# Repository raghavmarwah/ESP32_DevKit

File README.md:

# ESP32 Development Board Clone

This is project #3 for the course [KiCAD like a Pro](https://techexplorations.com/so/kicad-like-a-pro-3rd-edition/). In this project, I created my own version of the very popular [ESP32 development kit](https://docs.espressif.com/projects/esp-idf/en/latest/esp32/hw-reference/esp32/get-started-devkitc.html) using open source schematics provided by [espressif](https://www.espressif.com/en/support/documents/technical-documents?).
<br><br>
More information about my progress with the course: https://raghavmarwah.com/kicad-udemy-course/
<br>

## Schematics

## 2 layer PCB

## 3D render (front)

## 3D render (rear)

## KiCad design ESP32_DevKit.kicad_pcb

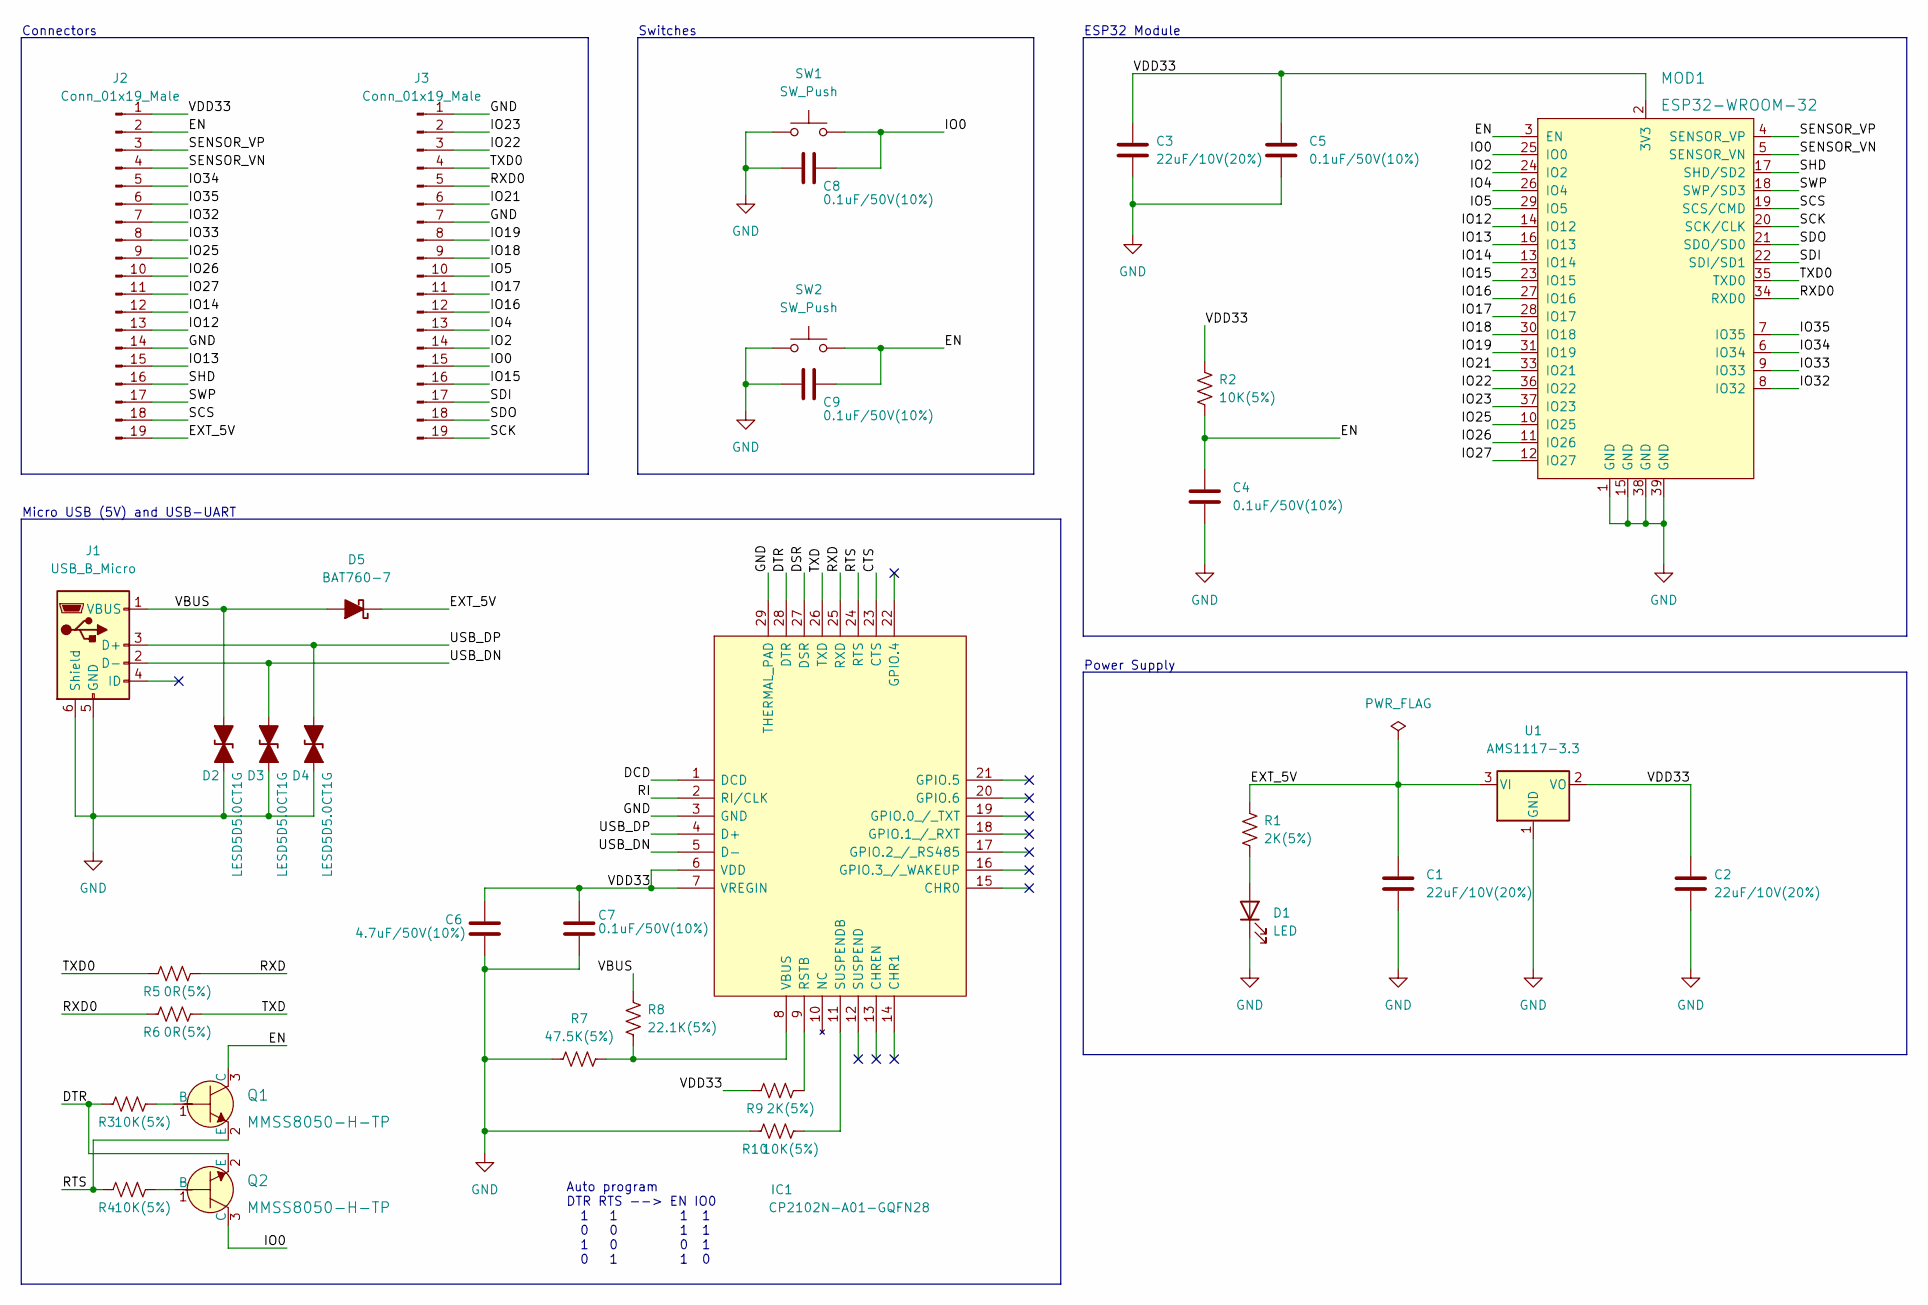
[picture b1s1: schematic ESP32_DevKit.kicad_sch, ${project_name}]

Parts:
C1, C2, C3: 22uF/10V(20%); C_0805_2012Metric_Pad1.18x1.45mm_HandSolder
C4, C5, C7, C8, C9: 0.1uF/50V(10%); C_0805_2012Metric_Pad1.18x1.45mm_HandSolder
C6: 4.7uF/50V(10%); C_0805_2012Metric_Pad1.18x1.45mm_HandSolder
D1: LED; LED_0805_2012Metric_Pad1.15x1.40mm_HandSolder
D2, D3, D4: LESD5D5.0CT1G; SODFL1608X70N
D5: BAT760-7; SOD2513X120N
IC1: CP2102N-A01-GQFN28; QFN50P500X500X80-29N-D; Manufacturer_Part_Number CP2102N-A01-GQFN28; Mouser Part Number 634-CP2102NA01GQFN28
J1: USB_B_Micro; USB_Micro-AB_Molex_47590-0001
J2, J3: Conn_01x19_Male; PinHeader_1x19_P2.54mm_Vertical
MOD1: ESP32-WROOM-32; ESP32-WROOM-32D; MPN ESP32-WROOM-32; Digi-Key_PN 1904-1010-1-ND
Q1, Q2: MMSS8050-H-TP; SOT-23-3; MPN MMSS8050-H-TP; Digi-Key_PN MMSS8050-H-TPMSCT-ND
R1, R9: 2K(5%); R_0805_2012Metric_Pad1.20x1.40mm_HandSolder
R2, R3, R4, R10: 10K(5%); R_0805_2012Metric_Pad1.20x1.40mm_HandSolder
R5, R6: 0R(5%); R_0805_2012Metric_Pad1.20x1.40mm_HandSolder
R7: 47.5K(5%); R_0805_2012Metric_Pad1.20x1.40mm_HandSolder
R8: 22.1K(5%); R_0805_2012Metric_Pad1.20x1.40mm_HandSolder
SW1, SW2: SW_Push; SW_Push_1P1T_NO_6x6mm_H9.5mm
U1: AMS1117-3.3; SOT-223-3_TabPin2

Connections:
/CTS: IC1.23 (CTS)
/DCD: IC1.1 (DCD)
/DSR: IC1.27 (DSR)
/DTR: IC1.28 (DTR), Q2.2 (E), R3.2
/EN: C4.1, C9.1, J2.2, MOD1.3 (EN), Q1.3 (C), R2.2, SW2.2
/EXT_5V: C1.1, D5.1 (K), J2.19, R1.1, U1.3 (VI)
/IO0: C8.1, J3.15, MOD1.25 (IO0), Q2.3 (C), SW1.2
/IO2: J3.14, MOD1.24 (IO2)
/IO4: J3.13, MOD1.26 (IO4)
/IO5: J3.10, MOD1.29 (IO5)
/IO12: J2.13, MOD1.14 (IO12)
/IO13: J2.15, MOD1.16 (IO13)
/IO14: J2.12, MOD1.13 (IO14)
/IO15: J3.16, MOD1.23 (IO15)
/IO16: J3.12, MOD1.27 (IO16)
/IO17: J3.11, MOD1.28 (IO17)
/IO18: J3.9, MOD1.30 (IO18)
/IO19: J3.8, MOD1.31 (IO19)
/IO21: J3.6, MOD1.33 (IO21)
/IO22: J3.3, MOD1.36 (IO22)
/IO23: J3.2, MOD1.37 (IO23)
/IO25: J2.9, MOD1.10 (IO25)
/IO26: J2.10, MOD1.11 (IO26)
/IO27: J2.11, MOD1.12 (IO27)
/IO32: J2.7, MOD1.8 (IO32)
/IO33: J2.8, MOD1.9 (IO33)
/IO34: J2.5, MOD1.6 (IO34)
/IO35: J2.6, MOD1.7 (IO35)
/RI: IC1.2 (RI/CLK)
/RTS: IC1.24 (RTS), Q1.2 (E), R4.2
/RXD: IC1.25 (RXD), R5.1
/RXD0: J3.5, MOD1.34 (RXD0), R6.2
/SCK: J3.19, MOD1.20 (SCK/CLK)
/SCS: J2.18, MOD1.19 (SCS/CMD)
/SDI: J3.17, MOD1.22 (SDI/SD1)
/SDO: J3.18, MOD1.21 (SDO/SD0)
/SENSOR_VN: J2.4, MOD1.5 (SENSOR_VN)
/SENSOR_VP: J2.3, MOD1.4 (SENSOR_VP)
/SHD: J2.16, MOD1.17 (SHD/SD2)
/SWP: J2.17, MOD1.18 (SWP/SD3)
/TXD: IC1.26 (TXD), R6.1
/TXD0: J3.4, MOD1.35 (TXD0), R5.2
/USB_DN: D3.2 (A2), IC1.5 (D-), J1.2 (D-)
/USB_DP: D4.2 (A2), IC1.4 (D+), J1.3 (D+)
/VBUS: D2.2 (A2), D5.2 (A), J1.1 (VBUS), R8.1
/VDD33: C2.1, C3.1, C5.1, C6.1, C7.1, IC1.6 (VDD), IC1.7 (VREGIN), J2.1, MOD1.2 (3V3), R2.1, R9.2, U1.2 (VO)
GND: C1.2, C2.2, C3.2, C4.2, C5.2, C6.2, C7.2, C8.2, C9.2, D1.1 (K), D2.1 (A1), D3.1 (A1), D4.1 (A1), IC1.3 (GND), IC1.29 (THERMAL_PAD), J1.5 (GND), J1.6 (Shield), J2.14, J3.1, J3.7, MOD1.1 (GND), MOD1.15 (GND), MOD1.38 (GND), MOD1.39 (GND), R7.1, R10.2, SW1.1, SW2.1, U1.1 (GND)
unnamed: D1.2 (A), R1.2
unnamed: IC1.8 (VBUS), R7.2, R8.2
unnamed: IC1.9 (RSTB), R9.1
unnamed: IC1.11 (SUSPENDB), R10.1
unnamed: Q1.1 (B), R3.1
unnamed: Q2.1 (B), R4.1

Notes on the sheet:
Power Supply
Switches
Connectors
Micro USB (5V) and USB-UART
ESP32 Module
Auto program DTR RTS --> EN IO0 1 1 1 1 0 0 1 1 1 0 0 1 0 1 1 0

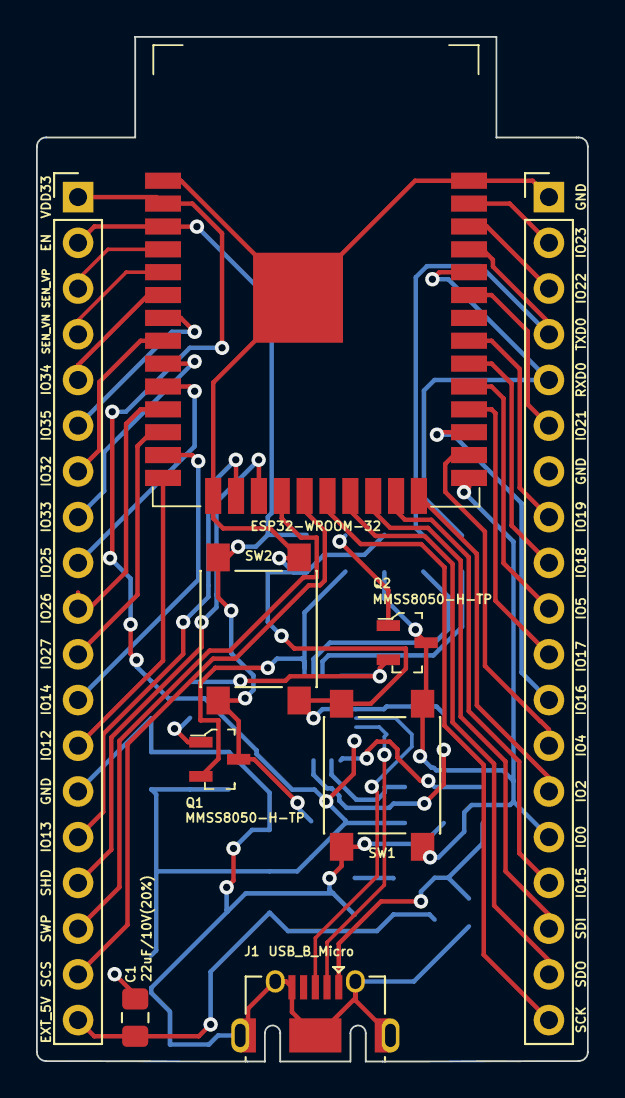
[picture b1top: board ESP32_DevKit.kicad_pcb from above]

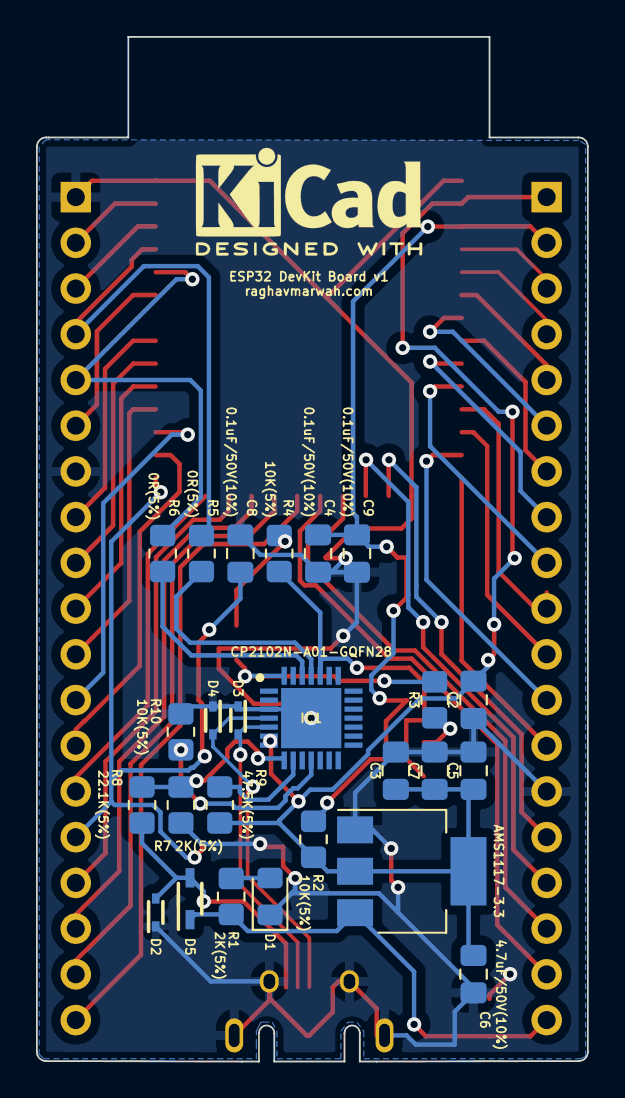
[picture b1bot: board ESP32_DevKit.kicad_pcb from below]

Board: 2 copper layers, 30.6 x 56.9 mm, 34 parts (25 on the bottom side), 49 nets.

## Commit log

2022-09-03 Created KiCad project
2022-09-04 Schematic design completed
2022-09-04 PCB design completed
2022-09-04 Added README.md
2022-09-04 Edited README.md
